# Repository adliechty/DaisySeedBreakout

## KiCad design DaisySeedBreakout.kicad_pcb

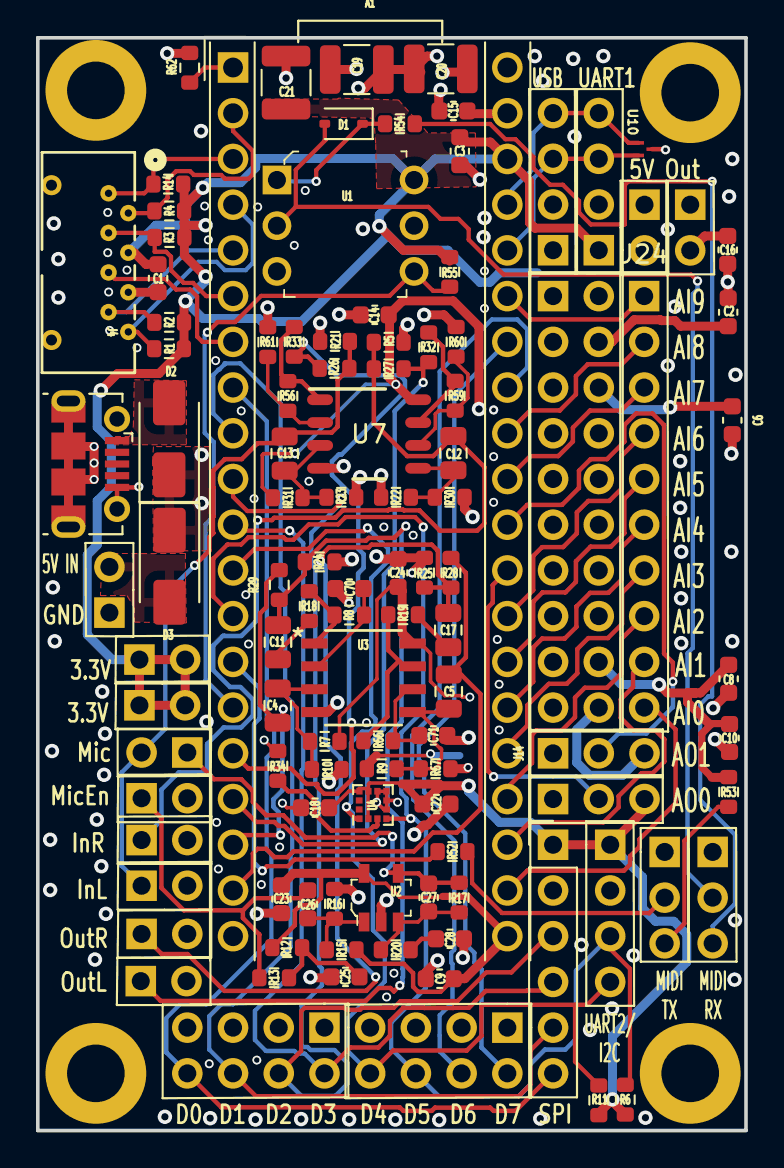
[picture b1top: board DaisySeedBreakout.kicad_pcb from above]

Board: 4 copper layers, 39.3 x 60.7 mm, 113 parts (0 on the bottom side), 71 nets.

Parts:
A1: Electrosmith_Daisy_Seed_Rev4; Electrosmith_Daisy_Seed
C1, C2, C3, C6, C8, C9, C10, C14, C15, C16, C18, C22, C23, C24, C25, C26: 0.1uF 0402; C_0603_1608Metric
C4, C5, C11, C12, C13, C17: 10U; C_0805_2012Metric
C19: 100uF; C_1210_3225Metric
C20, C21: DNP_100uF; C_1210_3225Metric
C27: 100pF COG; C_0603_1608Metric
C28: 1uF; C_0603_1608Metric
C70, C71: DNP; C_0603_1608Metric
D1: D_Schottky; D_SOD-323
D2, D3: SS54; D_SMA
H1, H2, H3, H4: MountingHole; MountingHole_3.2mm_M3_DIN965_Pad
J1, J3, J10, J14: Conn_01x03; PinHeader_1x03_P2.54mm_Vertical_Female
J2, J6, J8, J9, J11, J12, J13, J16, J17, J25, J26: Conn_01x02; PinHeader_1x02_P2.54mm_VerticalFemale
J4: Micro_SD_Card; CONN_PJS008U-3000-0_YAM
J5, J7, J20: Conn_01x04; PinHeader_1x04_P2.54mm_Vertical_Female
J15: USB_B_Micro; USB_Micro-B_Molex-105017-0001
J18, J21: Conn_02x04; PinHeader_2x04_P2.54mm_Vertical_Female
J19: Conn_01x06; PinHeader_1x06_P2.54mm_Vertical_Female
J23: Pins_02x10_P2.54mm_TH; PinHeader_2x10_P2.54mm_Vertical
J24: Conn_01x10; PinHeader_1x10_P2.54mm_Vertical_Female
R1, R2, R3, R4, R14: 47k; R_0603_1608Metric
R5, R7, R9, R10, R15, R16, R21, R22, R23, R24, R25, R30, R31, R67: 1M; R_0603_1608Metric
R6, R11, R20: 10k; R_0603_1608Metric
R8, R56, R59, R62, R66: 0; R_0603_1608Metric
R12, R13: 2.2k; R_0603_1608Metric
R17: 100k; R_0603_1608Metric
R18, R19: 100; R_0603_1608Metric
R26, R27, R28, R29, R34, R60, R61: DNP; R_0603_1608Metric
R32, R33: 4.7k; R_0603_1608Metric
R52: 10; R_0603_1608Metric
R53: 33; R_0603_1608Metric
R54: 220; R_0603_1608Metric
R55: 470; R_0603_1608Metric
U1: H11L1M; DIP-6_W7.62mm
U2: MAX4466EXK_T; SOT-353
U3: D8_TEX
U4: LIS2DE12; LGA-12_2x2mm_P0.5mm
U7: TLV9062IDR; D0008A_N
U10: TPD2EUSB30ADRTR; DRT3

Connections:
+3.3V: A1.38 (3V3_D), C1.1, C2.1, C3.1, C6.1, C8.1, C10.1, C18.1, C21.1, C22.1, J4.4 (VDD), J7.1, J10.3, J14.3, J19.1, J20.1, J23.2, J23.4, J23.6, J23.8, J23.10, J23.12, J23.14, J23.16, J23.18, J23.20, J25.1, J25.2, J26.1, J26.2, R1.1, R2.1, R3.1, R4.1, R6.1, R11.1, R14.1, R53.1, R55.2, U1.6 (VCC), U4.2 (~CS), U4.9 (Vdd), U4.10 (Vdd_IO)
+3.3VA: A1.21 (3V3_A), C9.1, C14.1, C23.1, C24.1, R7.1, R9.1, R12.2, R15.2, R30.1, R31.1, U2.5 (VCC), U3.8 (V+), U7.8 (V+)
+5V: A1.39 (VIN), C15.1, C16.1, C19.1, C20.1, D2.1 (K), D3.1 (K), J5.1, J9.1, J9.2, J16.1, J16.2
/AI_0: A1.22 (ADC_0), J24.10
/AI_1: A1.23 (ADC_1), J24.9
/AI_2: A1.24 (ADC_2), J24.8
/AI_3: A1.25 (ADC_3), J24.7
/AI_4: A1.26 (ADC_4), J24.6
/AI_5: A1.27 (ADC_5), J24.5
/AI_6: A1.28 (ADC_6), J24.4
/AI_7: A1.31 (SAI2_MCLK), J24.3
/AI_8: A1.32 (SAI2_SD_B), J24.2
/AI_9: A1.35 (SAI2_SCK), J24.1
/AO_0: A1.29 (DAC_OUT2), J10.2
/AO_1: A1.30 (DAC_OUT1), J14.2
/Audio In/L_in+: C13.2, R23.1, R31.2, U7.3 (IN+)
/Audio In/L_in-: R56.2, R61.1, U7.2 (IN-)
/Audio In/L_out+: R33.2, R56.1, U7.1 (OUT)
/Audio In/R_in+: C12.2, R22.1, R30.2, U7.5 (IN+)
/Audio In/R_in-: R59.2, R60.1, U7.6 (IN-)
/Audio In/R_out+: R32.2, R59.1, U7.7 (OUT)
/Audio Out/L_in+: C4.2, R7.2, R10.1, U3.3 (+IN_A)
/Audio Out/L_in-: C70.1, R8.1, U3.2 (-A)
/Audio Out/L_out: R8.2, R18.1, U3.1
/Audio Out/R_in+: C5.2, R9.2, R67.1, U3.5 (+IN_B)
/Audio Out/R_in-: C71.1, R66.1, U3.6 (-B)
/Audio Out/R_out: R19.1, R66.2, U3.7
/Audio_IN_1: A1.16 (AUDIO_IN_1), R26.1, R33.1
/Audio_IN_2: A1.17 (AUDIO_IN_2), R27.1, R32.1
/Audio_IN_L_CONN: C13.1, J8.2, J12.1, R21.1, R26.2
/Audio_IN_R_CONN: C12.1, J13.1, R5.1, R27.2
/Audio_OUT_1: A1.18 (AUDIO_OUT_1), C4.1, R29.2
/Audio_OUT_2: A1.19 (AUDIO_OUT_2), C5.1, R28.2
/Audio_OUT_L_CONN: C11.2, J2.1, R24.1, R29.1
/Audio_OUT_R_CONN: C17.2, J11.1, R25.1, R28.1
/Condensor Microphone/MIC_BIAS: C25.1, R12.1, R13.2
/Condensor Microphone/MIC_CONN: C26.1, J17.1, R13.1
/Condensor Microphone/MIC_IN+: C26.2, R15.1, R16.2, U2.1
/Condensor Microphone/MIC_IN-: C27.1, R17.2, R20.2, U2.3
/DIO0_CS: A1.8 (SPI1_CS), J19.6, J21.8
/DIO1_SCK: A1.9 (SPI1_SCK), J19.5, J21.6
/DIO2_POCI: A1.10 (SPI1_POCI), J19.3, J21.4
/DIO3_PICO: A1.11 (SPI1_PICO), J19.4, J21.2
/DIO4_SCL_RX: A1.12 (I2C1_SCL), J7.4, J18.8, R11.2, U4.1 (SCL/SPC)
/DIO5_SDA_TX: A1.13 (I2C1_SDA), J7.3, J18.6, R6.2, U4.4 (SDA/SDI)
/DIO6: A1.33 (SAI2_SD_A), J18.4
/DIO7: A1.34 (SAI2_FS), J18.2
/HEADER_5V: D3.2 (A), J6.2
/MIDI_IN_CONN: D1.2 (A), J3.2, U1.2
/MIDI_IN_CONN_R: J3.3, R54.2
/MIDI_IN_Diode: D1.1 (K), R54.1, U1.1
/MIDI_TX_CONN: J1.2, R52.2
/MIDI_TX_PWR: J1.3, R53.2
/MIDI_UART_RX: A1.15 (USART1_RX), R55.1, U1.4 (VO)
/MIDI_UART_TX: A1.14 (USART1_TX), R52.1
/Mic_OUT: C27.2, J8.1, R17.1, U2.4
/SD_CLK: A1.7 (SD_CLK), J4.5 (CLK)
/SD_CMD: A1.6 (SD_CMD), J4.3 (CMD), R3.2
/SD_D0: A1.5 (SD_DATA_0), J4.7 (DAT0), R2.2
/SD_D1: A1.4 (SD_DATA_1), J4.8 (DAT1), R1.2
/SD_D2: A1.3 (SD_DATA_2), J4.1 (DAT2), R14.2
/SD_D3: A1.2 (SD_DATA_3), J4.2 (DAT3/CD), R4.2
/USB_5V: D2.2 (A), J15.1 (VBUS)
/USB_n: A1.36 (USB_D_-), J5.3, J20.3, U10.2 (D-)
/USB_p: A1.37 (USB_D_+), J5.4, J20.4, U10.1 (D+)
GND: A1.20 (AGND), A1.40 (DGND), C1.2, C2.2, C3.2, C6.2, C8.2, C9.2, C10.2, C14.2, C15.2, C16.2, C18.2, C19.2, C20.2, C21.2, C22.2, C23.2, C24.2, C25.2, C28.1, C70.2, C71.2, H1.1, H2.1, H3.1, H4.1, J1.1, J2.2, J3.1, J4.6 (VSS), J5.2, J6.1, J7.2, J10.1, J11.2, J12.2, J13.2, J14.1, J15.5 (GND), J15.6 (Shield), J17.2, J18.1, J18.3, J18.5, J18.7, J19.2, J20.2, J21.1, J21.3, J21.5, J21.7, J23.1, J23.3, J23.5, J23.7, J23.9, J23.11, J23.13, J23.15, J23.17, J23.19, R5.2, R10.2, R16.1, R21.2, R22.2, R23.2, R24.2, R25.2, R34.1, R60.2, R61.2, R62.2, R67.2, U1.5 (GND), U2.2 (GND), U3.4 (V-), U4.5 (RES), U4.6 (GND), U4.7 (GND), U4.8 (GND), U7.4 (V-), U10.3 (GND)
unnamed: A1.1 (USB_ID), R62.1
unnamed: C11.1, R18.2
unnamed: C17.1, R19.2
unnamed: C28.2, R20.1
unnamed: R34.2, U4.3 (SA0/SDO)

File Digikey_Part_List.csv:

Digikey PN,Reference,Footprint,Value,Voltage,Type,Order Quantity,Total Price
2057-RS1-10-G-ND,A1,DaisySeedThroughHold:Electrosmith_Daisy_Seed,Electrosmith_Daisy_Seed_Rev4,,,4,1.84
490-10431-1-ND ,"C1, C2, C3, C6, C8, C9, C10, C14, C15, C16, C18, C22, C23, C24, C25, C26",Capacitor_SMD:C_0603_1608Metric,0.1uF,6V,X5R,16,0.19
1276-1096-1-ND,"C4, C5, C11, C12, C13, C17",Capacitor_SMD:C_0805_2012Metric,10U,16V,X5R,6,0.48
1276-1092-1-ND,C19,Capacitor_SMD:C_1210_3225Metric,100uF,6V,X5R,1,0.52
490-11282-1-ND,C27,Capacitor_SMD:C_0603_1608Metric,100pF,6V,COG,1,0.02
13-CS0603KRX7R7BB105CT-ND,C28,Capacitor_SMD:C_0603_1608Metric,1uF,6V,X5R,1,0.09
SD103BWSQ-7-F,D1,Diode_SMD:D_SOD-323,D_Schottky,,,1,0.07
SK54A-LTPMSCT-ND,"D2, D3",Diode_SMD_AKL:D_SMC,SS54,,5A:0.7V,2,0.48
1212-1090-ND,"J1, J3, J10, J14",FemaleHeaders:PinHeader_1x03_P2.54mm_Vertical_Female,Conn_01x03,,,4,1.28
1212-1089-ND,"J2, J6, J8, J9, J11, J12, J13, J16, J17, J25, J26",1x2FemaleVertical:PinHeader_1x02_P2.54mm_VerticalFemale,Conn_01x02,,,11,2.08
PJS008U-3000-0,J4,microSDVertical:CONN_PJS008U-3000-0_YAM,Micro_SD_Card,,,1,
1212-1092-ND,"J5, J7, J20",FemaleHeaders:PinHeader_1x04_P2.54mm_Vertical_Female,Conn_01x04,,,3,1.14
WM1399CT-ND,J15,Connector_USB:USB_Micro-B_Molex-105017-0001,USB_B_Micro,,,1,0.75
,"J18, J21",FemaleHeaders:PinHeader_2x04_P2.54mm_Vertical_Female,Conn_02x04,,,2,
1212-1095-ND,J19,Ultralibrarian:PinHeader_1x06_P2.54mm_Vertical_Female,Conn_01x06,,,1,0.47
1212-1247-ND,J23,2x10FemaleHeader:PinHeader_2x10_P2.54mm_Vertical,Pins_02x10_P2.54mm_TH,,,1,1.17
1212-1099-ND,J24,FemaleHeaders:PinHeader_1x10_P2.54mm_Vertical_Female,Conn_01x10,,,1,0.68
13-AC0603FR-1347KLCT-ND,"R1, R2, R3, R4, R14",Resistor_SMD:R_0603_1608Metric,47k,,,5,0.1
541-5248-1-ND,"R5, R7, R9, R10, R15, R16, R21, R22, R23, R24, R25, R30, R31, R67",Resistor_SMD:R_0603_1608Metric,1M,,,14,0.56
13-AC0603DR-0710KLCT-ND,"R6, R11, R20",Resistor_SMD:R_0603_1608Metric,10k,,,3,0.06
541-2969-1-ND,"R8, R56, R59, R62, R66",Resistor_SMD:R_0603_1608Metric,0,,,5,0.15
P2.2KGCT-ND,"R12, R13",Resistor_SMD:R_0603_1608Metric,2.2k,,,2,0.16
541-CRCW0603100KFKEBCCT-ND,R17,Resistor_SMD:R_0603_1608Metric,100k,,,1,0.02
CR0603-FX-1000ELFCT-ND,"R18, R19",Resistor_SMD:R_0603_1608Metric,100,,,2,0.04
13-RC0603FR-7W4K7LCT-ND,"R32, R33",Resistor_SMD:R_0603_1608Metric,4.7k,,,2,0.04
13-AF0603FR-0710RLCT-ND,R52,Resistor_SMD:R_0603_1608Metric,10,,,1,0.03
13-RC0603FR-1033RLCT-ND,R53,Resistor_SMD:R_0603_1608Metric,33,,,1,0.02
118-CR0603-FX-2200ELFCT-ND,R54,Resistor_SMD:R_0603_1608Metric,220,,,1,0.02
541-CRCW0603470RJNEACCT-ND,R55,Resistor_SMD:R_0603_1608Metric,470,,,1,0.01
H11L1-MQT-ND,U1,digikey-footprints:DIP-6_W7.62mm,H11L1M,,,1,0.4
MAX4466EXK+CT-ND,U2,digikey-footprints:SOT-353,MAX4466EXK_T,,,1,0.58
296-47272-1-ND,U3,Ultralibrarian:D8_TEX,~,,,1,0.97
497-15997-1-ND,U4,Package_LGA:LGA-12_2x2mm_P0.5mm,LIS2DE12,,,1,1.45
296-47857-1-ND,U7,D0008A_N,TLV9062IDR,,,1,0.42
296-28153-1-ND,U10,DRT3,TPD2EUSB30ADRTR,,,1,0.36

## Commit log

2023-09-22 First addition
2023-09-23 Fixed ultralibrarian library with capital letter difference
2023-09-23 added knob headers, MIDI in header
2023-09-24 added double high audio jack
2023-09-25 adding 3d models
2023-09-26 adding mono connectors, CV, and gate as well
2023-09-27 update design to use more headers. Need to figure out easy way to integrate connectors in modular but easy to use way without dangling wires
2023-09-28 added dual audio back in to prototype that concept
2023-09-30 Converted circuits to sub circuits. Removed MIDI connector, changed to header only
2023-09-30 Minor modifications
2023-10-01 Placeholder for speaker driver
2023-10-02 add input fuse holder, TVS, reverse diode protection, placeholder 5V LDO
2023-10-02 add usb host current limit and ESD diodes
2023-10-05 Add USB 5V switcher, adjust audio in circuit
2023-10-06 Update Audio out to switch between 1V ptp or 10V ptp based on jumper
2023-10-07 getting closer
2023-10-08 trying grid of female headers to reduce header count and enable plug in modules
2023-10-09 commit before simplifyting the board further
2023-10-09 simplified design, rely on external boards more to cover those cases
2023-10-10 started layout
2023-10-11 partially routed
2023-10-15 periodic update
2023-10-16 added dedicated SPI, UART, I2C connectors
2023-10-19 further connector exploration
2023-10-20 Layout routed, no DRC yet
2023-10-21 PCB cleanup, added accelerometer as easy sensor to begin with
2023-10-22 some cleanup
2023-10-23 updated parts with those available on jlpcb
2023-10-24 some PCB cleanup
2023-10-25 moving to through hole microSD connector vertical, and through hole daisy seed to cost optimize. Surface mount daisy seed headers seemed more expensive
2023-10-26 Moved everything to the top side
2023-10-27 periodic commit
2023-10-27 Minor updates
2023-10-29 making way to generate digikey and mouser boms...work in progress
2023-10-30 adding script to pull prices and availability from Mouser
2023-10-31 Mouser BOM rollup working
2023-11-02 digikey API for BOM seems to be working
2023-11-03 Exporting of Mouser, Digikey, and JLPCB BOMs seems to be working
2023-11-04 script working to generate Mouser, Digikey, and JLPCB BOMS
2023-11-05 minor cleanup
2023-11-10 PCB submitted for order

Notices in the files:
parts and their libraries:
Copyright 2016 Accelerated Designs. All rights reserved.
